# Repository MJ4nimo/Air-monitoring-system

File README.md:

# Air-monitoring-system
AMS
complete

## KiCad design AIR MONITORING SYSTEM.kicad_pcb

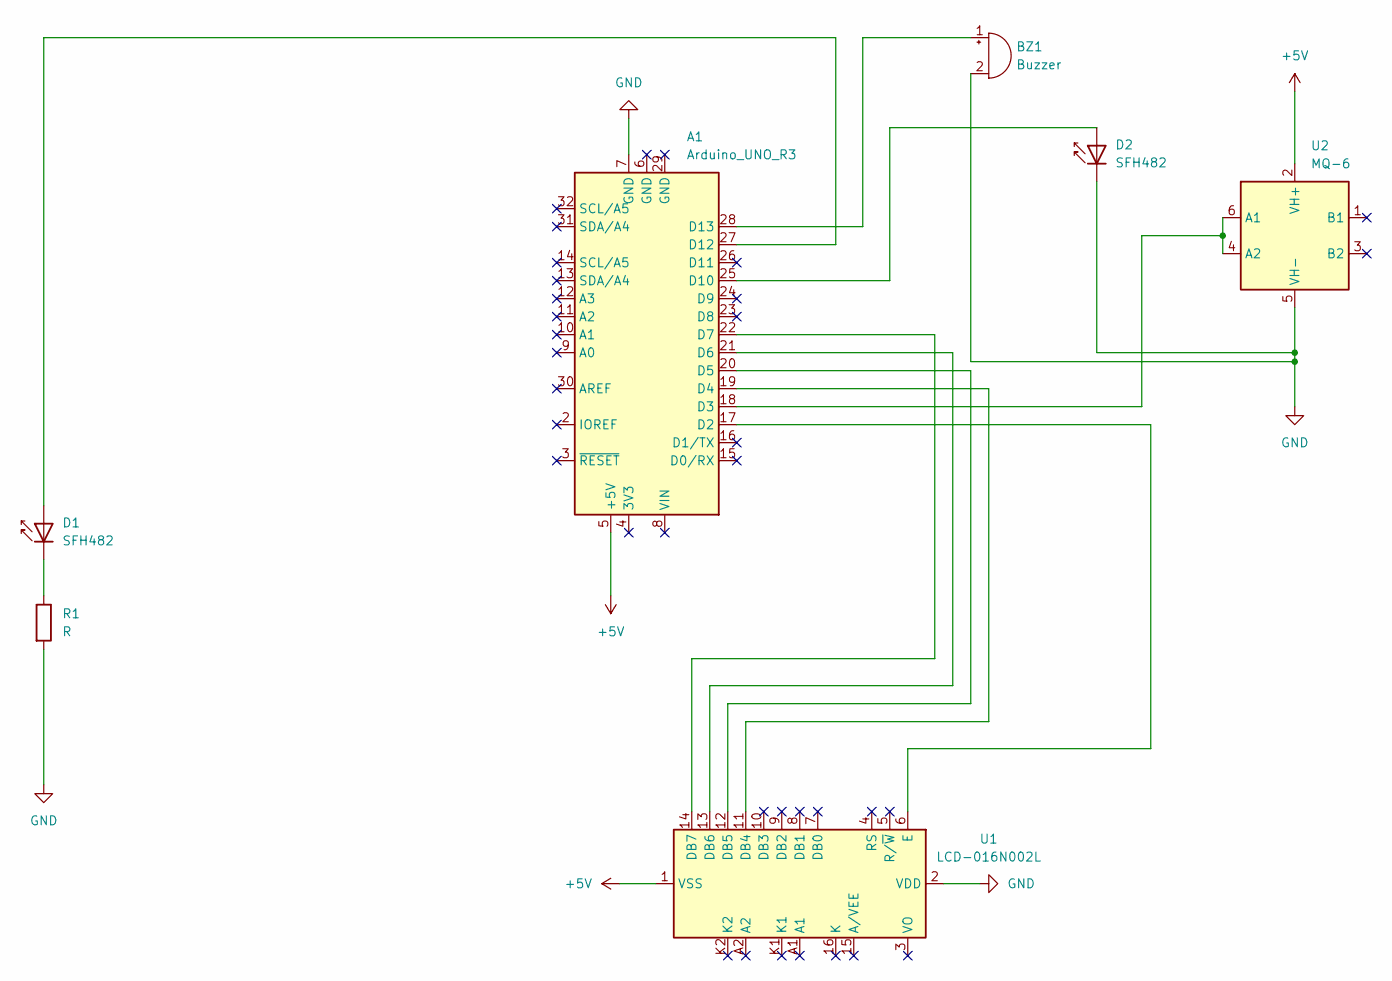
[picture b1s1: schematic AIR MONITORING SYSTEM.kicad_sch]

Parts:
A1: Arduino_UNO_R3
BZ1: Buzzer; Buzzer_12x9.5RM7.6
D1, D2: SFH482; TO-18-2_Window
R1: R; R_0201_0603Metric
U1: LCD-016N002L
U2: MQ-6

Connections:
+5V: A1.5 (+5V), U1.1 (VSS), U2.2 (VH+)
GND: A1.7 (GND), BZ1.2 (-), D2.1 (K), R1.2, U1.2 (VDD), U2.5 (VH-)
unnamed: A1.17 (D2), U1.6 (E)
unnamed: A1.18 (D3), U2.4 (A2), U2.6 (A1)
unnamed: A1.19 (D4), U1.11 (DB4)
unnamed: A1.20 (D5), U1.12 (DB5)
unnamed: A1.21 (D6), U1.13 (DB6)
unnamed: A1.22 (D7), U1.14 (DB7)
unnamed: A1.25 (D10), D2.2 (A)
unnamed: A1.27 (D12), D1.2 (A)
unnamed: A1.28 (D13), BZ1.1 (+)
unnamed: D1.1 (K), R1.1

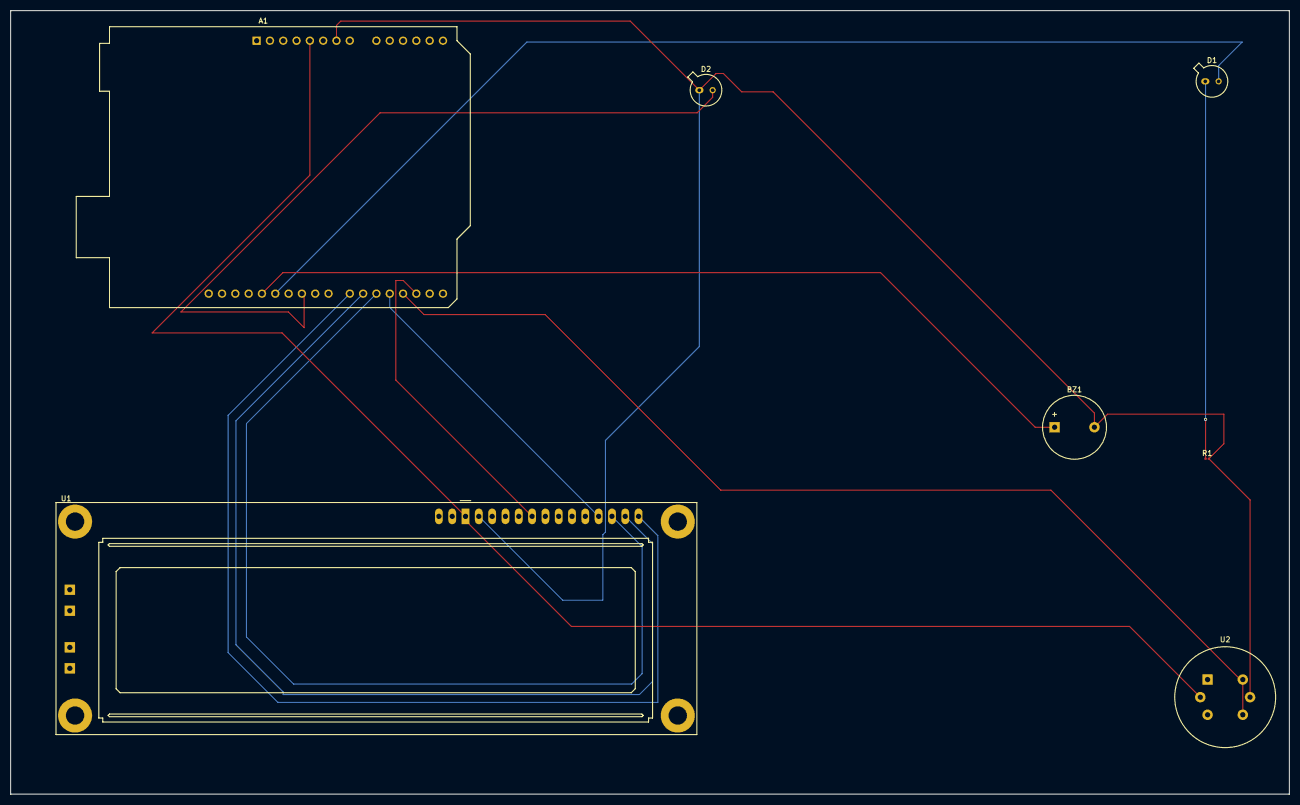
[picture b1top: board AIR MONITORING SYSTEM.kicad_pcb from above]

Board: 2 copper layers, 244.0 x 149.5 mm, 7 parts (0 on the bottom side), 12 nets.
